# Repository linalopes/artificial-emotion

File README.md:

# Artificial Emotion

**Artificial Emotion** is an ongoing artistic research project by **Lina Lopes** exploring how movement, soft mechanisms, sensing, bodily rhythms and material systems can produce expressive mechanical behaviour.

This repository is the working archive of the project. It brings together physical prototypes, fabrication files, electronics, code, research documentation and the source of the public research website.

## Research

The project currently develops through three connected research threads:

- **Soft Mechanisms**
- **Kinetic Studies**
- **Heartbeat & Biosignals**

These are not separate projects. They overlap through mechanisms, materials, sensing experiments, fabrication systems, public events and works in progress.

The research is intentionally documented while it is still changing.

## Repository structure

Some of the main areas of the repository are:

```text
artificial-emotion/
├── Site/
│   └── Public research website and Markdown-based research archive
│
├── kinetic-module-maumau/
│   └── Mau Mau kinetic module:
│       mechanical design, electronics, firmware and fabrication files
│
├── fixation-hackings/
│   └── Experimental mounting and attachment systems
│
├── homages/
│   └── Physical studies after existing kinetic works
│
├── little-heart-machine/
│   └── Folded paper heart and crank-plate fabrication files
│
├── artificial-emotion-controller-v1/
│   └── ESP32-S3 motor controller for kinetic experiments
│
└── README.md
```

The repository will continue to evolve as new studies, mechanisms and fabrication systems are developed.

## Public research site

The public documentation of the project is available at:

https://emotion.linalopes.info/

The site is built with **Astro** and uses **Markdown** as the primary content source. It functions as a public process archive rather than only as a presentation layer for finished work.

Its source lives in:

[`Site/`](Site/)

See [`Site/README.md`](Site/README.md) for the site architecture, content model, authoring rules and development setup.

## Run locally

The public site is the runnable part of this repository. From `Site/`:

```sh
cd Site
npm install        # once
npm run dev        # http://localhost:4321
```

Requires Node ≥ 22.12. Other useful commands:

```sh
npm run check      # type-check
npm run build      # static output in Site/dist/
npm run preview    # serve the built site
```

Cloudinary folder galleries (Research Threads) need credentials in `Site/.env`. Copy `Site/.env.example` and restart `npm run dev` after changing it. Those variables are used at build time only.

## Kinetic Module — Mau Mau

[`kinetic-module-maumau/`](kinetic-module-maumau/)

**Mau Mau** is an early kinetic research unit developed to study movement, rhythm, hesitation, repetition and mechanical tension.

The module combines mechanical design, electronics and control experiments around a compact actuation system.

Its folder contains work including:

- Rhino and Grasshopper mechanical design
- a parametric laser-cut enclosure
- a parametric 3D-printed spool
- ESP32-S3 / ULN2003 / 28BYJ-48 motor experiments
- homing and microswitch tests
- Arduino firmware
- an experimental KiCad PCB

See [`kinetic-module-maumau/README.md`](kinetic-module-maumau/README.md) for the detailed technical documentation.

## Controller v1

[`artificial-emotion-controller-v1/`](artificial-emotion-controller-v1/)

A modular **ESP32-S3** board for driving one 28BYJ-48 stepper motor and connecting sensors during kinetic experiments.

The first revision is through-hole, so it can be assembled, repaired and modified by hand. See [`artificial-emotion-controller-v1/README.md`](artificial-emotion-controller-v1/README.md) for the hardware notes, KiCad sources and fabrication checklist.

## Fixation Hackings

[`fixation-hackings/`](fixation-hackings/)

This area collects experimental mounting, clamping and attachment solutions developed as the project begins to require a shared physical infrastructure for suspending, rearranging and exhibiting prototypes.

These parts are treated as research objects too: small fabrication decisions can determine how modular, adaptable or reusable the larger installation becomes.

## Homages

[`homages/`](homages/)

Physical studies that begin from existing kinetic works and then become independent experiments inside Artificial Emotion. Fabrication files stay here; the editorial Studies live in `Site/content/studies/`.

Current folders:

- [`homages/ora-x-homage/`](homages/ora-x-homage/) — after Bruno Munari’s *Ora X*
- [`homages/c-15-homage/`](homages/c-15-homage/) — after Abraham Palatnik’s *Objeto Cinético C-15*

## Little Heart Machine

[`little-heart-machine/`](little-heart-machine/)

Cutting templates and a 3D-printed crank plate for the folded paper heart study.

## Documentation as part of the research

Artificial Emotion is documented while it is being developed.

The repository therefore contains both technical working files and editorial research material: prototypes, references, mechanisms, experiments, unfinished systems, failures and decisions that may still change.

Markdown, Git and the public website are used as part of that process rather than only as final publication tools.

The intention is to keep the research legible while it remains open.

## Status

**Active research.**

Files in this repository should not be assumed to represent final installation designs or production-ready hardware unless explicitly marked as such.

## Artist

**Lina Lopes**  
Artist, creative technologist and researcher

https://www.linalopes.info/

## Links

- Artificial Emotion — https://emotion.linalopes.info/
- Repository — https://github.com/linalopes/artificial-emotion
- Lina Lopes — https://www.linalopes.info/
- School of Tomorrow's AI — https://schoolai.linalopes.info/

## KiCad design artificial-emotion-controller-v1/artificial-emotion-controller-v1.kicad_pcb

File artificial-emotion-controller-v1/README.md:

# Artificial Emotion Controller v1

A modular, ESP32-S3-based motor controller designed by Lina Lopes for the **Artificial Emotion** research project.

The controller drives one 28BYJ-48 5V stepper motor and provides sensor interfaces for interactive kinetic experiments.

The first version prioritizes manual assembly, prototyping, and repairability.

## 1. Hardware Architecture

### Microcontroller

- ESP32-S3 SuperMini
- USB-C programming interface
- Integrated onboard LEDs
- Removable module mounted on pin sockets
- Battery functionality reserved for a future revision

### Motor Control

- ULN2003A, DIP-16
- One 28BYJ-48 5V unipolar stepper motor
- 5-pin JST-XH motor connector
- Four optional motor-phase indicator LEDs, each with a 2.2kΩ resistor

The motor-phase LEDs are independent indication circuits. The motor operates normally if the LEDs and their resistors are not installed.

## 2. Sensor Interfaces

The controller provides five general-purpose sensor connections organized into two banks, plus a dedicated I²C interface.

### Bank A — 3.3V Sensors

Four 3-pin male headers, 2.54mm pitch.

| Port | GPIO | Connections |
|---|---|---|
| A1 | GPIO1 | Signal / 3V3 / GND |
| A2 | GPIO2 | Signal / 3V3 / GND |
| A3 | GPIO4 | Signal / 3V3 / GND |
| A4 | GPIO5 | Signal / 3V3 / GND |

These inputs support analog and digital sensors operating with 3.3V-compatible signals.

### Bank B — 5V Sensor

One 3-pin male header, 2.54mm pitch.

| Port | GPIO | Connections |
|---|---|---|
| B1 | GPIO6 | Signal / 5V / GND |

The signal is connected to the ESP32-S3 through a voltage divider:

- 10kΩ series resistor
- 15kΩ resistor to GND
- 5V input signal reduced to approximately 3V

This interface is intended for 0–5V analog signals and suitable digital inputs, not arbitrary 5V digital communication protocols.

### Bank C — I²C

One 4-pin male header, 2.54mm pitch.

| Function | Connection |
|---|---|
| SDA | GPIO8 |
| SCL | GPIO9 |
| Power | 3V3 |
| Ground | GND |

## 3. GPIO Assignment

| GPIO | Function |
|---|---|
| GPIO1 | Sensor A1 |
| GPIO2 | Sensor A2 |
| GPIO4 | Sensor A3 |
| GPIO5 | Sensor A4 |
| GPIO6 | Sensor B1 (5V sensor signal via divider) |
| GPIO7 | USER button |
| GPIO8 | I²C SDA |
| GPIO9 | I²C SCL |
| GPIO10 | Motor IN1 |
| GPIO11 | Motor IN2 |
| GPIO12 | Motor IN3 |
| GPIO13 | Motor IN4 |

GPIO3 is not assigned. TX and RX remain unused.

## 4. User Interface

### USER Button

- Momentary normally-open tactile switch
- Connected between GPIO7 and GND
- Uses the ESP32-S3 internal pull-up resistor
- Silkscreen label: `BTN · IO7`

### Indicator LEDs

- Four optional motor-phase LEDs
- One external 5V power indicator LED
- ESP32-S3 onboard LEDs remain available

## 5. Power Architecture

The first revision uses an external regulated 5V DC supply.

### External Power

- Two-position screw terminal
- Shared GND
- JP1: external 5V to ESP32
- JP2: external 5V to motor
- 100µF electrolytic bulk capacitor
- 100nF ceramic decoupling capacitor

The jumpers allow the motor and ESP32 to be powered independently during testing.

**USB-C and external 5V must not be connected simultaneously with JP1 closed until the power-path behavior is verified.**

### Battery — Future Revision

The ESP32-S3 SuperMini includes battery connection pads, but battery operation is not implemented in this revision.

A future version may include:

- JST battery connection
- 1S LiPo battery
- 5V boost converter for the motor
- Power-source selection and protection

## 6. Construction

Version 1 uses predominantly through-hole technology (THT) to support manual soldering and experimentation.

- THT resistors
- 3mm THT LEDs
- THT capacitors
- THT tactile button
- DIP-16 motor driver
- Male pin headers for sensors and jumpers
- Four PCB mounting holes

## 7. KiCad Project

Project name: `artificial-emotion-controller-v1`

Designed in KiCad 10.

### Project Libraries

The ESP32-S3 SuperMini uses project-local symbol and footprint libraries:

- `esp32-s3-supermini.kicad_sym`
- `esp32-s3-supermini.pretty/`

All other components use standard KiCad libraries.

The project retains:

- `sym-lib-table`
- `fp-lib-table`

The earlier custom `AE.kicad_sym` library is no longer required, provided no remaining schematic symbols reference it.

## 8. Fabrication

The controller is designed as a two-layer PCB for manual component assembly.

Before each manufacturing release:

- [ ] Run ERC
- [ ] Run PCB DRC
- [ ] Check for unconnected nets
- [ ] Confirm footprints and component dimensions
- [ ] Verify motor connector pin order
- [ ] Review silkscreen, polarity markings, and mounting holes
- [ ] Inspect Gerber and Excellon drill files

The first version does not include battery circuitry or the 5V boost converter.

---

**Artificial Emotion Controller v1**
Designed by Lina Lopes
2026

Part of the Artificial Emotion research project.

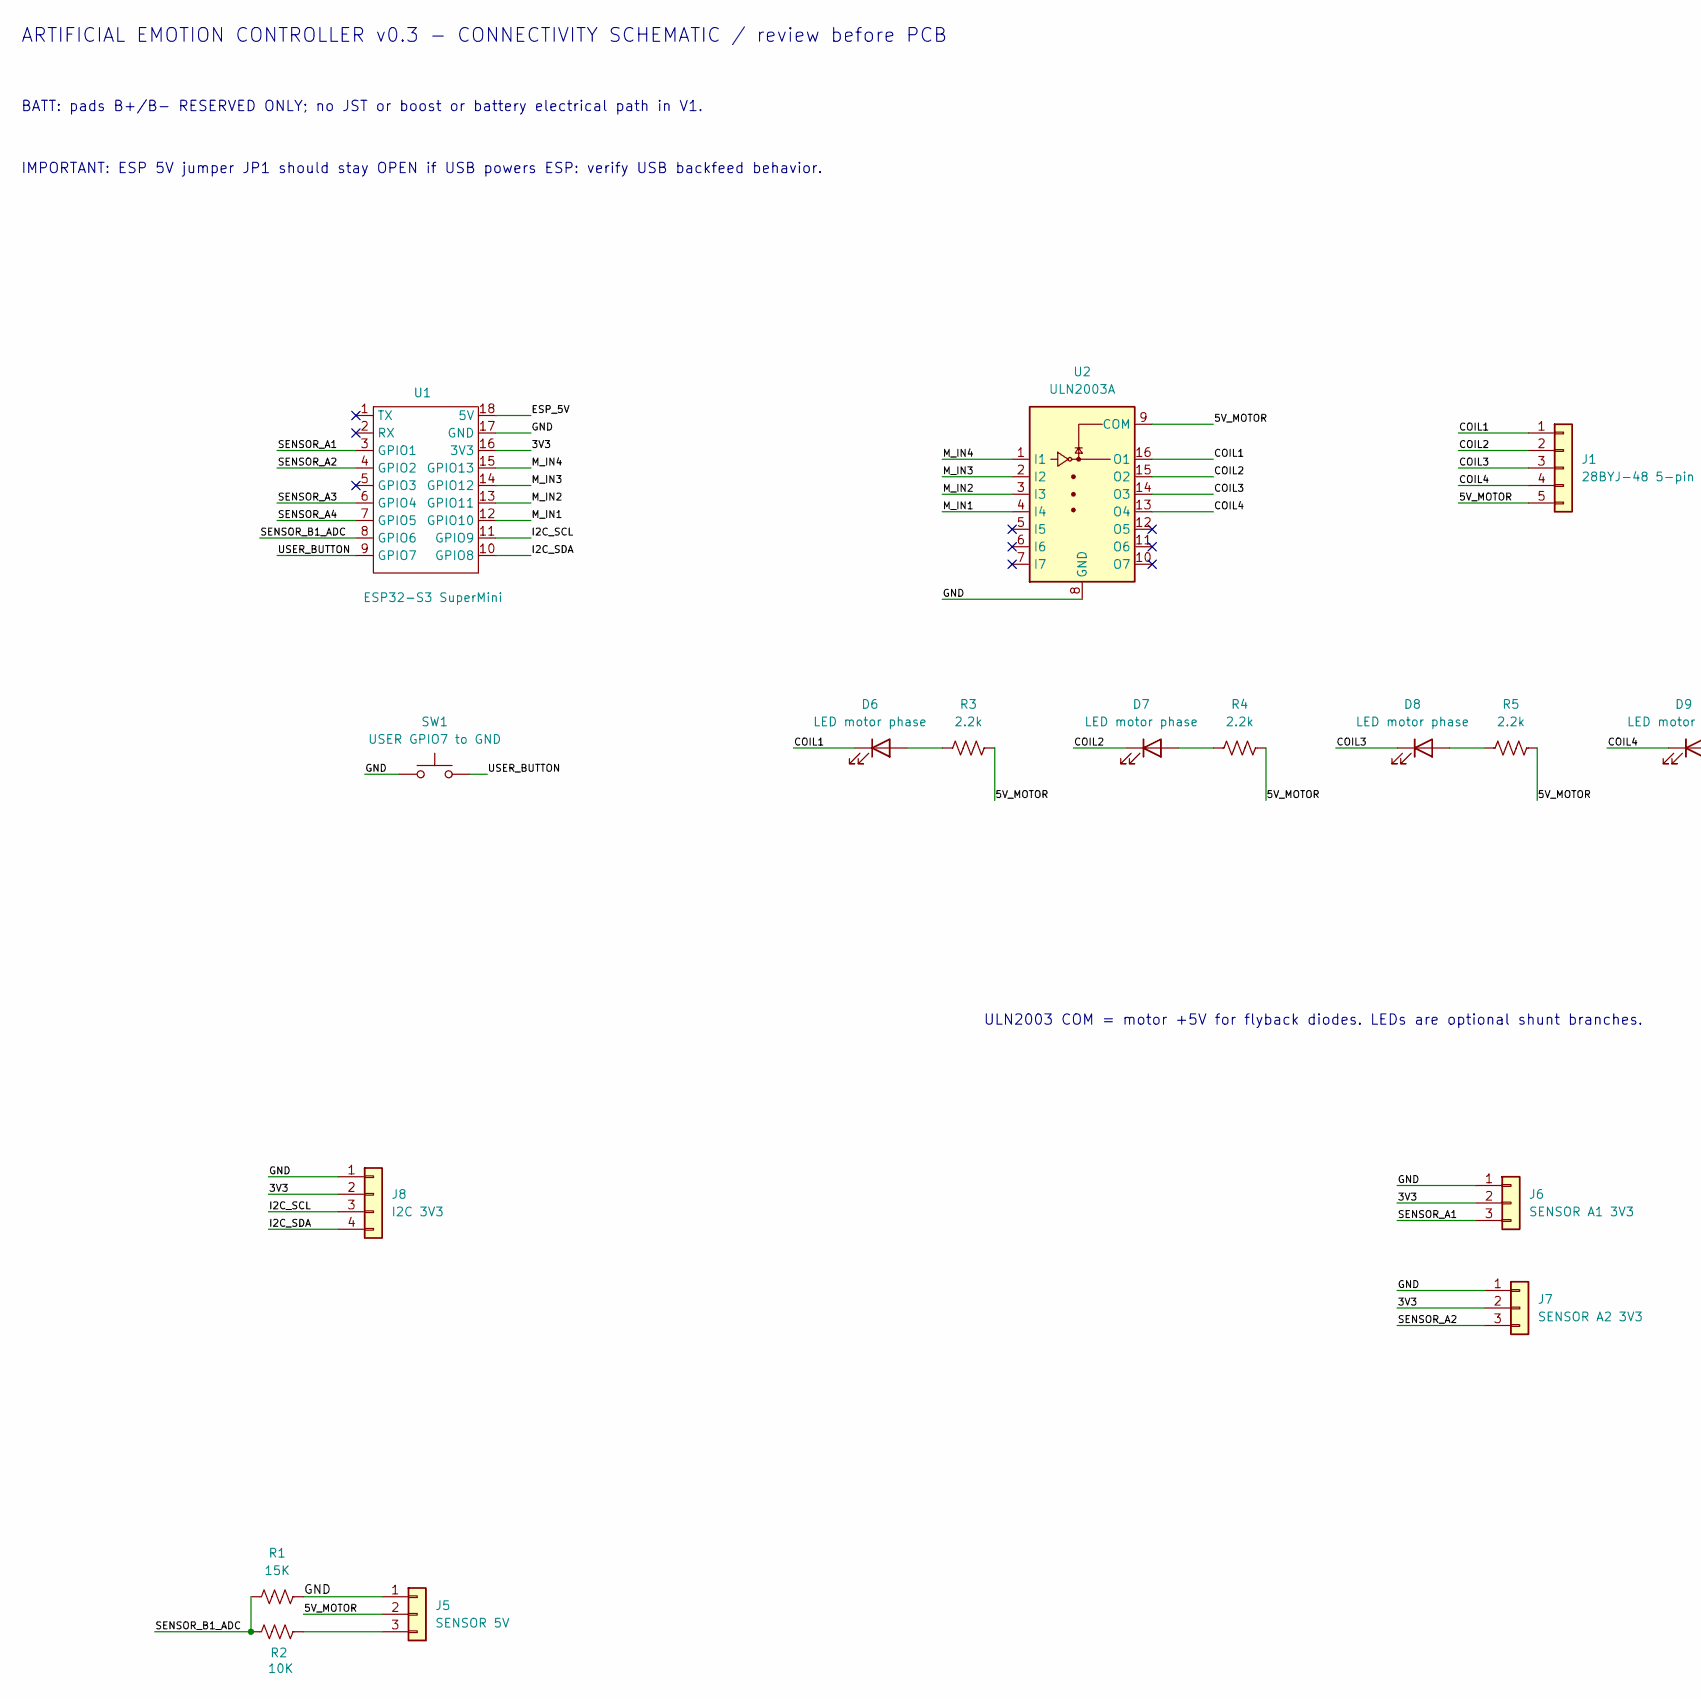
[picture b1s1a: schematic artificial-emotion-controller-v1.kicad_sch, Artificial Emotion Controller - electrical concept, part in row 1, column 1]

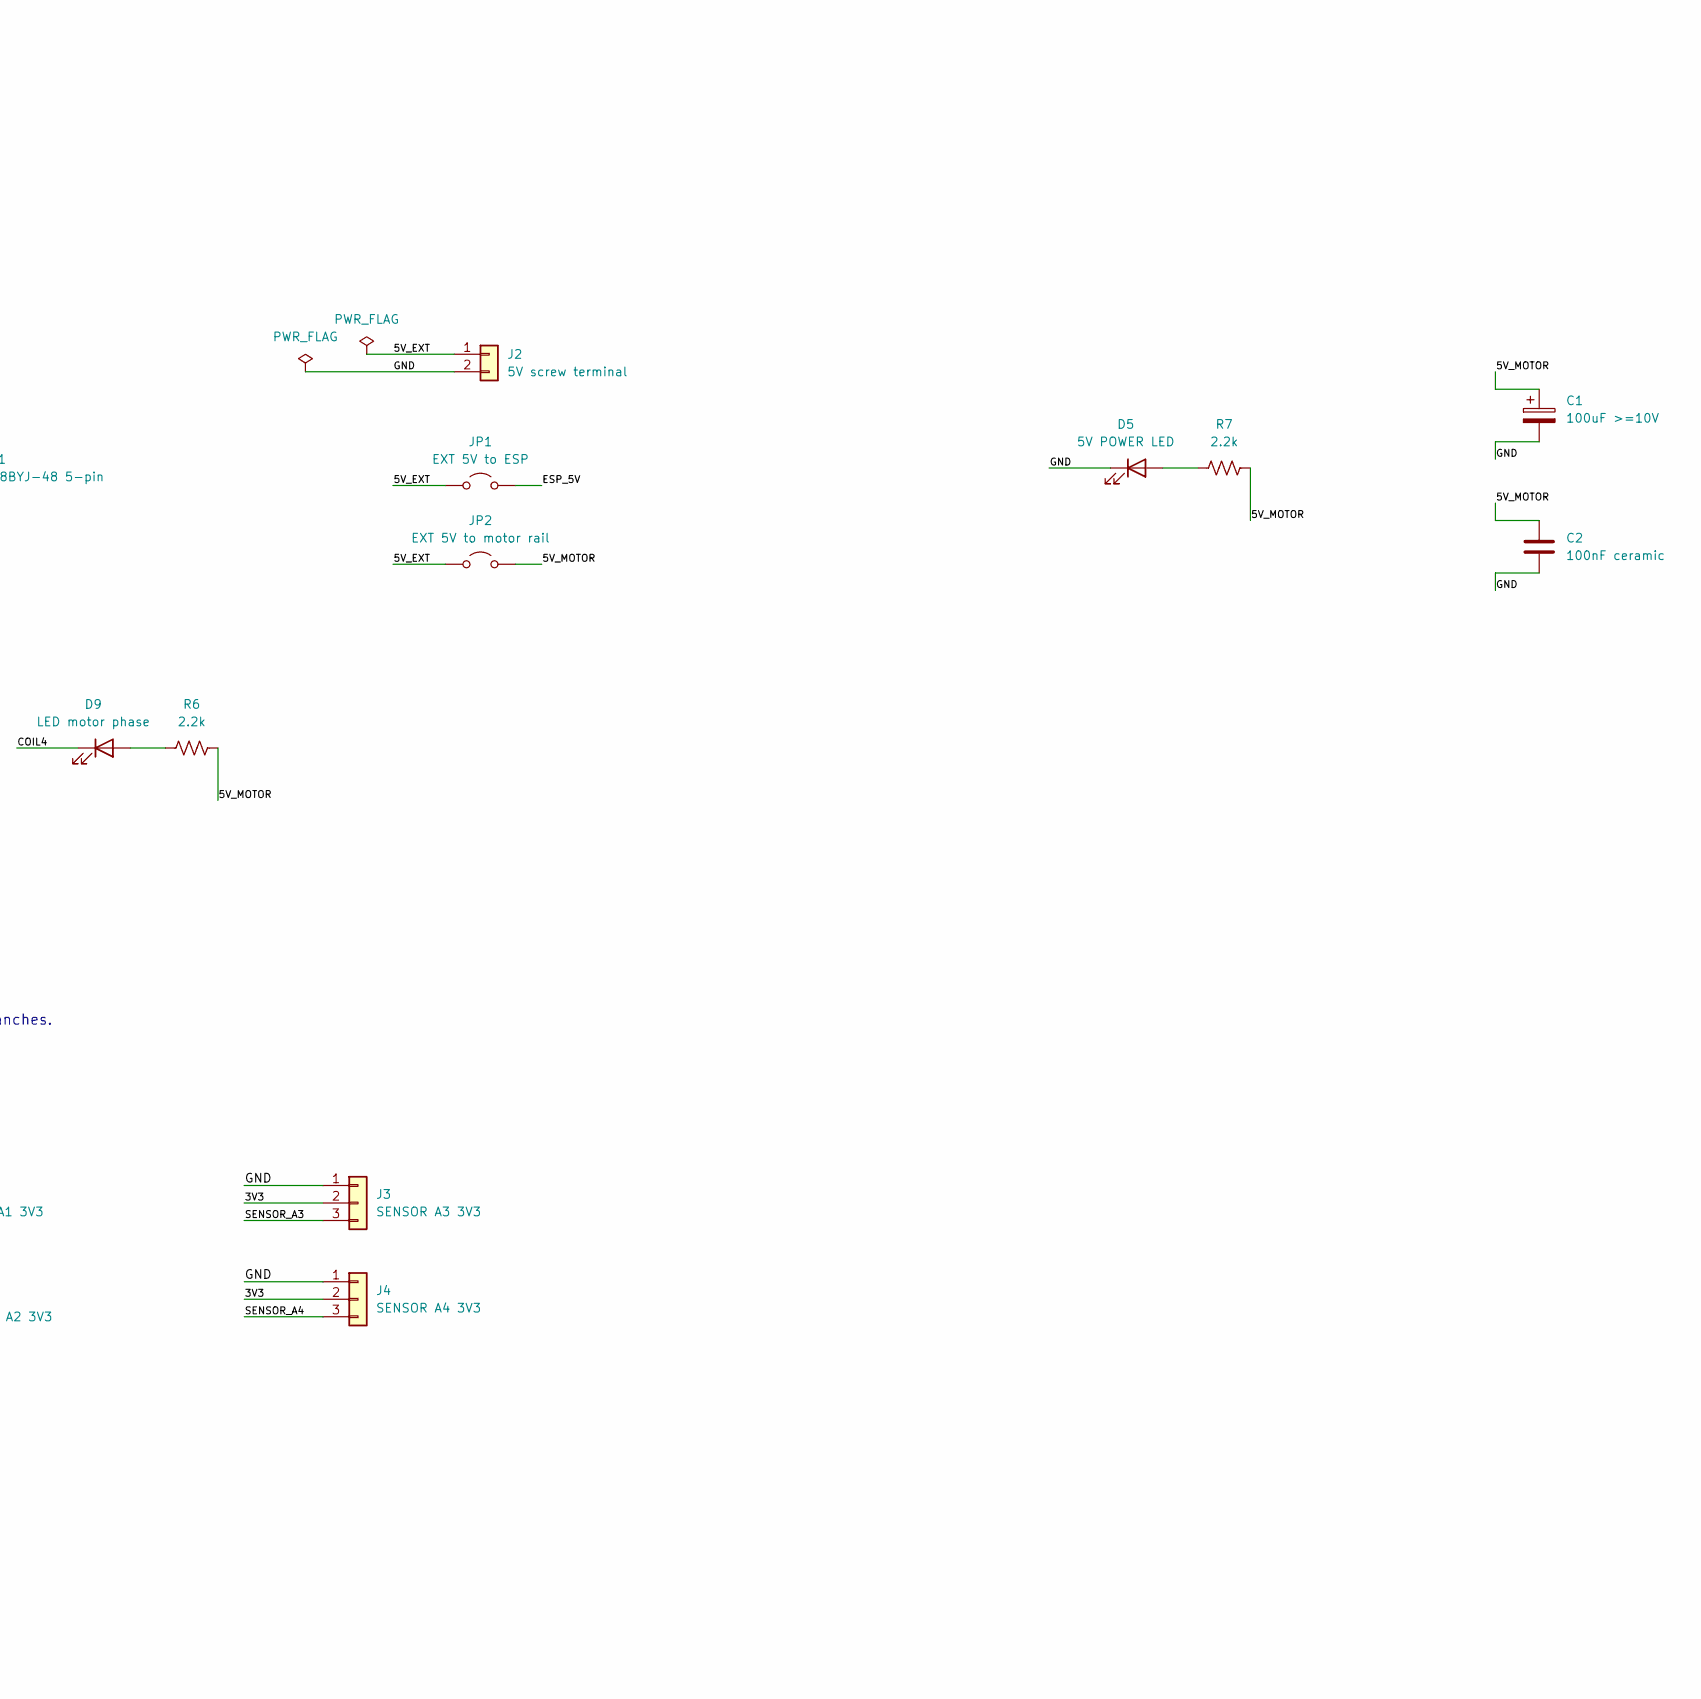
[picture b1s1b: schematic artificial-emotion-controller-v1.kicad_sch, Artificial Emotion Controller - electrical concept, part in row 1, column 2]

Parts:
C1: 100uF >=10V; CP_Radial_D6.3mm_P2.50mm
C2: 100nF ceramic; C_Disc_D5.0mm_W2.5mm_P5.00mm
D5: 5V POWER LED; LED_D3.0mm
D6, D7, D8, D9: LED motor phase; LED_D3.0mm
J1: 28BYJ-48 5-pin; JST_XH_B5B-XH-A_1x05_P2.50mm_Vertical
J2: 5V screw terminal; TerminalBlock_CUI_TB007-508-02_1x02_P5.08mm_Horizontal
J3: SENSOR A3 3V3; PinHeader_1x03_P2.54mm_Vertical
J4: SENSOR A4 3V3; PinHeader_1x03_P2.54mm_Vertical
J5: SENSOR 5V; PinHeader_1x03_P2.54mm_Vertical
J6: SENSOR A1 3V3; PinHeader_1x03_P2.54mm_Vertical
J7: SENSOR A2 3V3; PinHeader_1x03_P2.54mm_Vertical
J8: I2C 3V3; PinHeader_1x04_P2.54mm_Vertical
JP1: EXT 5V to ESP; PinHeader_1x02_P2.54mm_Vertical
JP2: EXT 5V to motor rail; PinHeader_1x02_P2.54mm_Vertical
R1: 15K; R_Axial_DIN0207_L6.3mm_D2.5mm_P7.62mm_Horizontal
R2: 10K; R_Axial_DIN0207_L6.3mm_D2.5mm_P7.62mm_Horizontal
R3, R4, R5, R6, R7: 2.2k; R_Axial_DIN0207_L6.3mm_D2.5mm_P7.62mm_Horizontal
SW1: USER GPIO7 to GND; SW_PUSH_6mm
U1: ESP32-S3 SuperMini; ESP32-S3_SuperMini_THT
U2: ULN2003A; DIP-16_W7.62mm

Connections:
/3V3: J3.2, J4.2, J6.2, J7.2, J8.2, U1.16 (3V3)
/5V_EXT: J2.1, JP1.1 (A), JP2.1 (A)
/5V_MOTOR: C1.1, C2.1, J1.5, J5.2, JP2.2 (B), R3.1, R4.1, R5.1, R6.1, R7.1, U2.9 (COM)
/COIL1: D6.1 (K), J1.1, U2.16 (O1)
/COIL2: D7.1 (K), J1.2, U2.15 (O2)
/COIL3: D8.1 (K), J1.3, U2.14 (O3)
/COIL4: D9.1 (K), J1.4, U2.13 (O4)
/ESP_5V: JP1.2 (B), U1.18 (5V)
/GND: C1.2, C2.2, D5.1 (K), J2.2, J3.1, J4.1, J5.1, J6.1, J7.1, J8.1, R1.1, SW1.1, U1.17 (GND), U2.8 (GND)
/I2C_SCL: J8.3, U1.11 (GPIO9)
/I2C_SDA: J8.4, U1.10 (GPIO8)
/M_IN1: U1.12 (GPIO10), U2.4 (I4)
/M_IN2: U1.13 (GPIO11), U2.3 (I3)
/M_IN3: U1.14 (GPIO12), U2.2 (I2)
/M_IN4: U1.15 (GPIO13), U2.1 (I1)
/SENSOR_A1: J6.3, U1.3 (GPIO1)
/SENSOR_A2: J7.3, U1.4 (GPIO2)
/SENSOR_A3: J3.3, U1.6 (GPIO4)
/SENSOR_A4: J4.3, U1.7 (GPIO5)
/SENSOR_B1_ADC: R1.2, R2.2, U1.8 (GPIO6)
/USER_BUTTON: SW1.2, U1.9 (GPIO7)
unnamed: D5.2 (A), R7.2
unnamed: D6.2 (A), R3.2
unnamed: D7.2 (A), R4.2
unnamed: D8.2 (A), R5.2
unnamed: D9.2 (A), R6.2
unnamed: J5.3, R2.1

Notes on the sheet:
IMPORTANT: ESP 5V jumper JP1 should stay OPEN if USB powers ESP: verify USB backfeed behavior.
ARTIFICIAL EMOTION CONTROLLER v0.3 - CONNECTIVITY SCHEMATIC / review before PCB
BATT: pads B+/B- RESERVED ONLY; no JST or boost or battery electrical path in V1.
ULN2003 COM = motor +5V for flyback diodes. LEDs are optional shunt branches.

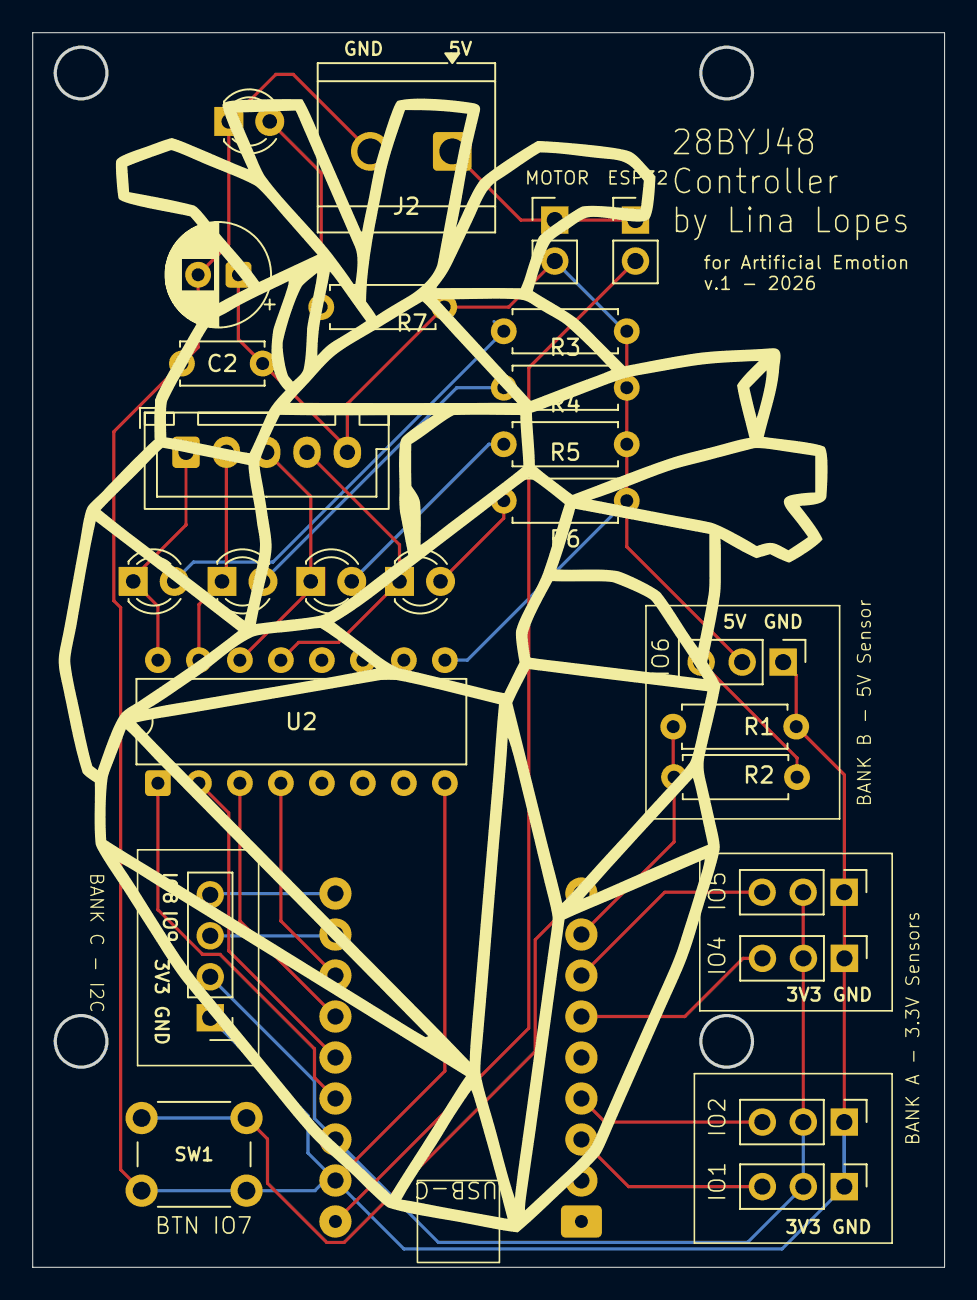
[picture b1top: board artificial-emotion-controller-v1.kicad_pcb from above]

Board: 2 copper layers, 56.5 x 76.5 mm, 27 parts (0 on the bottom side), 27 nets.

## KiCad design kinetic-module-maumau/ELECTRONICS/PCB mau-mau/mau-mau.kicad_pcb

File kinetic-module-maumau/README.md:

# Artificial Emotion — Kinetic Module

This folder documents **Mau Mau**, the first kinetic research unit of *Artificial Emotion*: a physical prototype for studying how a small computational system might express itself through movement, rhythm, hesitation, and material tension rather than through screens or language.

It is a working prototype, not the finished installation.

## About Artificial Emotion

*Artificial Emotion* is an artistic research project by **Lina Lopes**, developed during her artist residency at the [Institute for Future Technologies (IFT), De Vinci Higher Education](https://ift.devinci.fr/about), in Paris.

The project investigates the space between artificial intelligence, physiological sensing, mechanical behavior, embodied interaction, and material systems — and what humans interpret as emotional or living behavior.

A broader question behind the work is:

> What happens when a computational system is not only represented through screens, data, or language, but begins to express itself through physical rhythm, movement, hesitation, repetition, tension, and bodily behavior?

The heart and heartbeat belong to that wider research context. The project is also looking at ways of listening to and measuring the heart — including modalities such as ECG, PPG, PCG, pulse, and HRV — and at how physiological signals might later be translated into physical or kinetic behavior.

**This repository does not implement heartbeat sensing.** The kinetic module is not currently heartbeat-controlled. Physiological sensing belongs to the broader *Artificial Emotion* research and may later become an input to the kinetic system.

## Research Whiteboard

[**Open the live Artificial Emotion research whiteboard in Canva →**](https://canva.link/vxelx5a5ojinxqn)

## Why a Kinetic Module?

The final physical architecture of *Artificial Emotion* is still open.

One current hypothesis is an installation made from approximately 6–8 independent kinetic modules. That is a research direction, not a decision. The eventual work could instead use several independent motorized units, coordinated repeated actuators, fewer motors controlling multiple lines, a more centralized mechanical architecture, or another arrangement discovered through prototyping.

This repository exists to develop **one reproducible mechanical module** first:

1. build a physical research unit
2. understand its movement
3. solve its fabrication
4. understand line management
5. test homing and limits
6. prototype electronics and control
7. learn from the physical behavior
8. only then decide how a larger installation should scale

## Current Prototype

The current module investigates a simple vertical actuation chain.

```text
28BYJ-48 stepper motor
        ↓
   custom spool
        ↓
 braided fishing line
        ↓
    guide pulley
        ↓
 vertical moving / suspended element
        ↓
   home / endstop
```

The spool attaches directly to the 28BYJ-48 shaft. The guide pulley redirects the fishing line into the vertical path. A microswitch provides a mechanical home / endstop reference. A future sliding-tube / flange mechanism is intended to interact with that switch for homing; that mechanism is not finished in this repository.

## Repository Structure

```text
kinetic-module-maumau/
├── box-lasercutting.3dm
├── box-lasercutting.gh
├── spool-3dprinting.3dm
├── spool-3dprinting.gh
├── spool.stl
├── DESIGNS/
│   └── box-lasercutting-v2.gh
└── ELECTRONICS/
    ├── Arduino-motor-test/
    │   └── Arduino-motor-test.ino
    └── PCB mau-mau/
        ├── mau-mau.kicad_pro
        ├── mau-mau.kicad_sch
        ├── mau-mau.kicad_pcb
        ├── fp-lib-table
        ├── esp32-s3-supermini.kicad_sym
        └── esp32-s3-supermini.pretty/
            └── ESP32-S3_SuperMini_THT.kicad_mod
```

Mechanical design is authored in **Rhino 8** and **Grasshopper**. Electronics include bench-test firmware and an experimental KiCad project.

## Mechanical Design

### Enclosure

Original design sources: `box-lasercutting.3dm`, `box-lasercutting.gh`  
V2 fabrication definition: `kinetic-module-maumau/DESIGNS/box-lasercutting-v2.gh`

The Grasshopper definitions develop a parametric laser-cut enclosure for the kinetic module. The V2 work extends the original design with modular OS20 mounting patterns and a direct-to-SVG fabrication pipeline.

Current prototype dimensions are approximately:

| | |
|---|---|
| Width | 100 mm |
| Height | 80 mm |
| Depth | 60 mm |
| Material | 3 mm sheet |

The enclosure is designed without glue, using mechanical joints and captive-nut T-slot construction.

Current parts:

- Top
- Bottom
- Left
- Right
- Internal Divider
- Microswitch Bracket

There is no external Back panel in the current design. The front and rear remain open.

In V2, the Top uses a center-derived OS20 mounting pattern with **four primary Ø4.5 mm M4 clearance holes on a 40 × 40 mm rectangle**, plus **two optional holes**. `ExtraMountHoles` is currently enabled, giving six Top mounting holes. The upper enclosure joint axes have been raised by **0.5 mm**, and the captive nuts may project approximately **0.3 mm above the Top**. A perfectly flush ceiling-facing surface should therefore not be assumed without addressing that protrusion.

The Internal Divider is the mounting plane for the motor and guide pulley. Viewed from the open front:

- the 28BYJ-48 body sits behind the Divider
- the shaft projects through the Divider toward the front
- the spool sits on the shaft in front of the Divider

### V2 enclosure changes

The V2 design retains the six physical sheet parts, the 3 mm material system, and the front/rear openings. Its current features include:

| Feature | V2 specification |
|---|---|
| Upper enclosure joints | Screw axes shifted +0.5 mm; existing M3 captive-nut joints retained |
| Bottom guide opening | Square **6 × 6 mm**, intended to reduce rotation of a future sliding tube |
| Top mounting grid | OS20, **six Ø4.5 mm** M4 clearance holes with `ExtraMountHoles = True` |
| Right universal mounting plate | **Ten Ø3.2 mm** holes on a PCB-anchored 20 mm grid: four PCB positions plus six additional positions |
| Left universal mounting plate | **Eight Ø3.2 mm** holes on an optimized 20 mm grid |

The **Right panel** has four PCB-reference centers forming a **40 × 60 mm** rectangle. These four holes are geometrically non-overlapping but have a minimum material ligament of approximately **2.265 mm**, below the project's **3 mm** screening policy. They remain explicit, documented *PCB clearance exceptions*, not ordinary passes or proof of mechanical strength. Two other Right grid positions were omitted because they overlap Divider slots.

The **Left panel** has eight mounting holes that pass the existing 3 mm geometric-ligament rule; a ninth candidate was omitted because of its proximity to a microswitch-bracket mounting opening. The two lateral patterns differ because their existing openings differ.

The mounting holes make the enclosure more adaptable to PCBs, sensors, and small mechanical accessories. **Bare-hole clearance does not certify the fit of screw heads, spacers, board outlines, or attached components.** The intended PCB mounts on the *exterior* of the Right panel, but its complete physical fit still requires verification. In particular, the previously documented approximate PCB body size and the proposed 40 × 60 mm mounting-hole spacing should be checked against the actual KiCad design before claiming they describe the same board.

The Bottom square opening is a guide interface only. The matching sliding tube and its homing behavior remain under development.

### Laser fabrication workflow (V2)

The V2 definition has a **direct Grasshopper-to-SVG exporter**, which **does not require baking geometry into Rhino**:

- `1300`: canonical six-part 2D layout and SVG serializer; uses kerf-compensated source curves
- `1305`: `ExportFabricationSvg` Boolean Toggle; exporting while `True` may rewrite the output on subsequent Grasshopper recomputations
- `1306`: exporter report
- `1312`: translated Top-view preview, **not** the export source

The latest validated setup contains **67 closed cutting curves for all six parts**, with no duplicates or open paths. It uses a **500 × 250 mm** sheet, **5 mm** margins/spacing, **1:1 millimetre SVG** output, and **0.15 mm full-kerf compensation applied once**. The preview's sheet boundary, construction geometry, labels, and engraving are excluded from the SVG. The red line visible in Rhino's Top viewport was identified as the construction-plane X-axis, not fabrication geometry.

The export target was subsequently requested to be changed to the **same folder as the active `.gh` file**, retaining the filename `kinetic-module-v2-fabrication-layout.svg`. Verify the resolved path in the exporter report: the latest conversation confirms the *request*, not that the path change was implemented and saved. Likewise, SVG export or Git commit status must be verified in the repository rather than assumed.

The older fabrication workflow included experimental multi-sheet nesting. V2 instead uses a simpler direct layout, avoiding an automatic nesting step.

### Spool

Sources: `spool-3dprinting.3dm`, `spool-3dprinting.gh`  
Export: `spool.stl`

The spool is a custom parametric part designed to attach directly to the 28BYJ-48 output shaft using a double-flat profile.

Current approximate dimensions:

| | |
|---|---|
| Core diameter | 15 mm |
| Core width | 5 mm |
| Flange diameter | 24 mm |
| Flange thickness | 1.8 mm |
| Exported STL envelope | approximately 24 × 24 × 8.6 mm |

The Grasshopper definition also includes shaft tolerance, insertion depth, motor-side flange transition, fishing-line diameter, and a parametric line-anchor hole (radial and angular position). The current line used during prototyping is approximately 0.24 mm braided fishing line. The anchor is a localized through-hole in the flange opposite the motor-side flange.

`spool.stl` is older than the current Rhino / Grasshopper sources (export dated 2026-09-18; sources updated 2026-09-22). Regenerate the STL from the current definition before treating the mesh as the latest version.

## Electronics

The project currently contains two related electronics approaches. They should not be confused.

### 1. Prototype wiring

The currently tested prototype uses a ready-made ULN2003 driver module with:

- ESP32-S3 Super Mini
- ULN2003 driver module
- 28BYJ-48 5 V stepper
- KW11-style microswitch
- 5 V power

Tested pin mapping:

| ESP32-S3 | Function |
|---|---|
| GPIO4 | ULN2003 IN1 |
| GPIO5 | ULN2003 IN2 |
| GPIO6 | ULN2003 IN3 |
| GPIO7 | ULN2003 IN4 |
| GPIO8 | home switch (INPUT_PULLUP, active LOW) |

This is the wiring assumed by the bench-test firmware.

### 2. Experimental custom PCB

`kinetic-module-maumau/ELECTRONICS/PCB mau-mau/` is a KiCad experiment named **mau-mau**. It explores integrating the ESP32-S3 Super Mini, a bare ULN2003 DIP-16, a +5 V / GND screw-terminal input, and a power-indicator LED with series resistor onto a small custom board. The earlier README described its body as approximately 40 × 42 mm; the V2 Right mounting study instead used a provisional 40 × 60 mm four-hole pattern. **The actual PCB outline and mounting-hole coordinates must be rechecked in KiCad** before treating these descriptions as compatible.

The board includes a custom symbol and through-hole footprint for the ESP32-S3 Super Mini. Silkscreen on the layout reads *Kinetic Module / Mau Mau / by Lina Lopes*.

**This PCB is not a production controller.** In the current KiCad files:

- ULN2003 outputs are not brought to a motor connector
- GPIO8 / the home-switch input is not exposed
- Gerbers, drill files, and a BOM export are not present

Treat it as an experimental alternative to the ready-made ULN2003 module, still in progress.

## Firmware

File: [`kinetic-module-maumau/ELECTRONICS/Arduino-motor-test/Arduino-motor-test.ino`](kinetic-module-maumau/ELECTRONICS/Arduino-motor-test/Arduino-motor-test.ino)

This is bench-test firmware for the prototype wiring above. It is not installation firmware.

It currently tests:

- 28BYJ-48 movement through a ULN2003
- half-step coil sequencing
- motion in both directions (8 seconds each way, with a pause between)
- home-switch detection on GPIO8
- motor release when idle or when the switch is triggered

Pin map in the sketch:

```text
IN1      = GPIO4
IN2      = GPIO5
IN3      = GPIO6
IN4      = GPIO7
HOME_PIN = GPIO8
```

## Current Hardware

| Item | Role in the current prototype |
|---|---|
| ESP32-S3 Super Mini | microcontroller |
| 28BYJ-48, 5 V | geared stepper motor |
| ULN2003 | motor driver (ready-made module in the tested prototype; DIP-16 on the experimental PCB) |
| KW11-style microswitch | mechanical home / endstop |
| V-groove guide pulley (~3 mm bore, 12 mm OD, 4 mm width) | redirects the line into the vertical path |
| 5 V power supply | motor and logic supply |
| Braided fishing line (~0.24 mm) | actuation line |
| 3 mm sheet material | laser-cut enclosure and microswitch bracket |
| Custom 3D-printed spool | couples the motor shaft to the line |

Motor dimensions currently used as mechanical reference: body Ø28 × ~19 mm; mounting holes Ø4 mm at 35 mm centers; shaft/boss axis offset 8 mm from the mounting-ear / body centerline; boss Ø9 mm; nominal shaft Ø5 mm with an approximately 3 mm flat.

The guide pulley is mounted on the front of the Internal Divider with an M3 screw. Its exact position remains parametric.

The microswitch bracket is laser-cut from the same 3 mm sheet. Current assembly, from the open front: bracket → microswitch body → Internal Divider. The roller remains accessible to a future vertical sliding mechanism.

## Fabrication

### 3D printing

The spool is the 3D-printed part. Sources are `spool-3dprinting.3dm` and `spool-3dprinting.gh`. An STL export is present as `spool.stl`; re-export from the current definition before printing if you need the latest geometry.

### Laser cutting

The enclosure and microswitch bracket are designed for 3 mm sheet. V2 fabrication is authored in `kinetic-module-maumau/DESIGNS/box-lasercutting-v2.gh`. Its exporter directly writes kerf-compensated SVG cutting paths for all six pieces, without Bake. Verify the actual output path and exported file before sending it to a laser cutter. The exporter is configured for millimetres at 1:1; confirm the physical dimensions in the laser software before cutting. The source README does not establish whether an SVG has been committed to the repository.

### PCB

The experimental `mau-mau` KiCad project can be opened from `kinetic-module-maumau/ELECTRONICS/PCB mau-mau/`. Production fabrication outputs (Gerbers, drill files, BOM) are not committed.

## Status

**Current status: active research prototype.**

Represented now:

- parametric laser-cut enclosure, including V2 OS20 mounting patterns on Top and both sides
- direct Grasshopper SVG workflow validated for six pieces / 67 cutting curves
- parametric 3D-printed spool
- motor-test firmware
- experimental KiCad PCB

Still evolving:

- sliding-tube / flange homing mechanism
- final pulley, guide-hole, and switch relationship
- confirmation and version control of the final V2 SVG export; regeneration of the current spool STL
- production firmware
- finalized controller PCB
- physiological sensing / heartbeat interface
- module count
- larger installation architecture

## Design Philosophy

The repository uses parametric fabrication and modular prototyping on purpose. Motor offset, line path, pulley position, switch placement, and enclosure joints are treated as relationships that can still move as the artistic research develops. One physical unit is being made understandable before the larger work is locked.

## Credits

**Lina Lopes**  
Artist / researcher

*Artificial Emotion*

Artist residency:  
[Institute for Future Technologies (IFT)](https://ift.devinci.fr/about)  
De Vinci Higher Education  
Paris, France

[De Vinci Foundation](https://foundation.devinci.fr/)

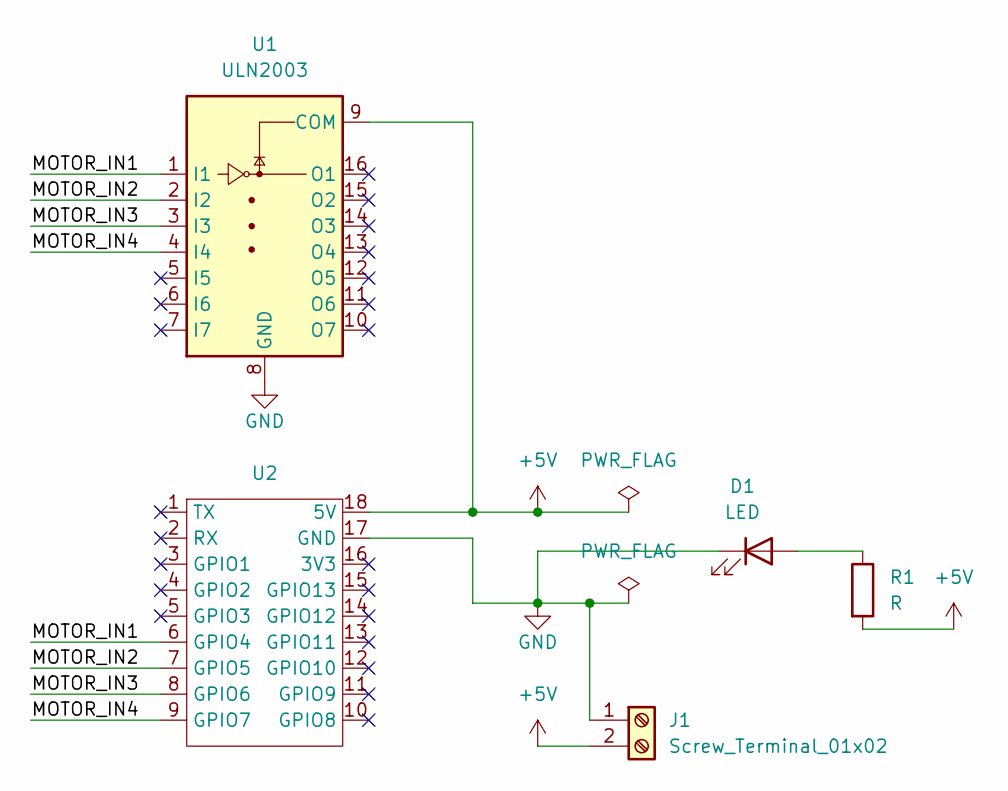
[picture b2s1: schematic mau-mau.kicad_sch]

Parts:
D1: LED; LED_D3.0mm
J1: Screw_Terminal_01x02; TerminalBlock_Phoenix_MKDS-1,5-2-5.08_1x02_P5.08mm_Horizont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
R1: R; R_Axial_DIN0207_L6.3mm_D2.5mm_P7.62mm_Horizontal
U1: ULN2003; DIP-16_W7.62mm
U2: ESP32-S3_SuperMini_THT

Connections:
+5V: J1.2, R1.2, U1.9 (COM), U2.18 (5V)
/MOTOR_IN1: U1.1 (I1), U2.6 (GPIO4)
/MOTOR_IN2: U1.2 (I2), U2.7 (GPIO5)
/MOTOR_IN3: U1.3 (I3), U2.8 (GPIO6)
/MOTOR_IN4: U1.4 (I4), U2.9 (GPIO7)
GND: D1.1 (K), J1.1, U1.8 (GND), U2.17 (GND)
unnamed: D1.2 (A), R1.1

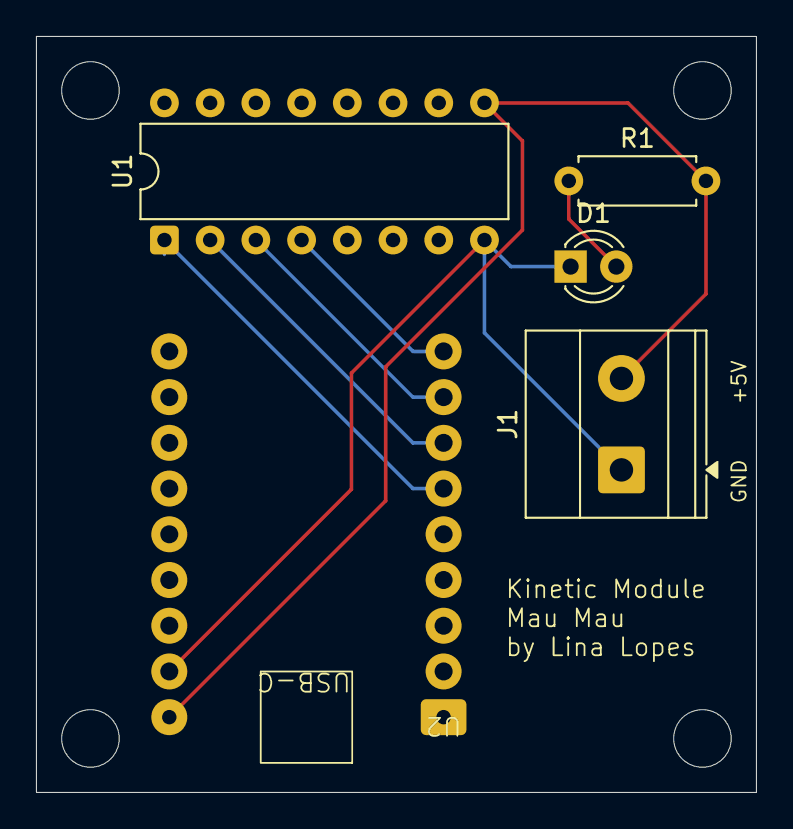
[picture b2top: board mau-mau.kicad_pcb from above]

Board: 2 copper layers, 40.0 x 42.0 mm, 5 parts (0 on the bottom side), 7 nets.
